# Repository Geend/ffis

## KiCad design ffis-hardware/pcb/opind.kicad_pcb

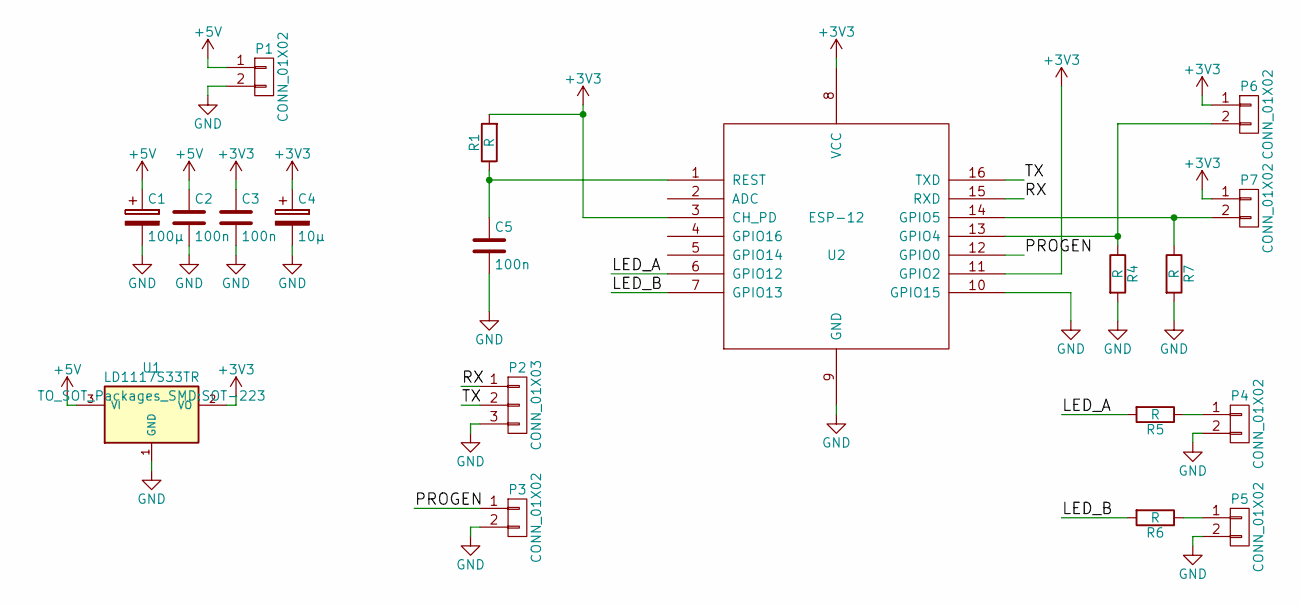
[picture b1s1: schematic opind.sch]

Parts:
C1: 100µ; c_elec_6.3x5.7
C2, C3, C5: 100n; C_0603_HandSoldering
C4: 10µ; c_elec_4x5.8
P1, P3, P4, P5, P6, P7: CONN_01X02; Pin_Header_Straight_1x02
P2: CONN_01X03; Pin_Header_Straight_1x03
R1, R4, R5, R6, R7: R; R_0603_HandSoldering
U1: LD1117S33TR; SOT-223
U2: ESP-12

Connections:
+3V3: C3.1, C4.1, P6.1, P7.1, R1.2, U1.2 (VO), U2.3 (CH_PD), U2.8 (VCC), U2.11 (GPIO2)
+5V: C1.1, C2.1, P1.1, U1.3 (VI)
/LED_A: R5.2, U2.6 (GPIO12)
/LED_B: R6.2, U2.7 (GPIO13)
/PROGEN: P3.1, U2.12 (GPIO0)
/RX: P2.1, U2.15 (RXD)
/TX: P2.2, U2.16 (TXD)
GND: C1.2, C2.2, C3.2, C4.2, C5.2, P1.2, P2.3, P3.2, P4.2, P5.2, R4.2, R7.2, U1.1 (GND), U2.9 (GND), U2.10 (GPIO15)
unnamed: C5.1, R1.1, U2.1 (REST)
unnamed: P4.1, R5.1
unnamed: P5.1, R6.1
unnamed: P6.2, R4.1, U2.13 (GPIO4)
unnamed: P7.2, R7.1, U2.14 (GPIO5)

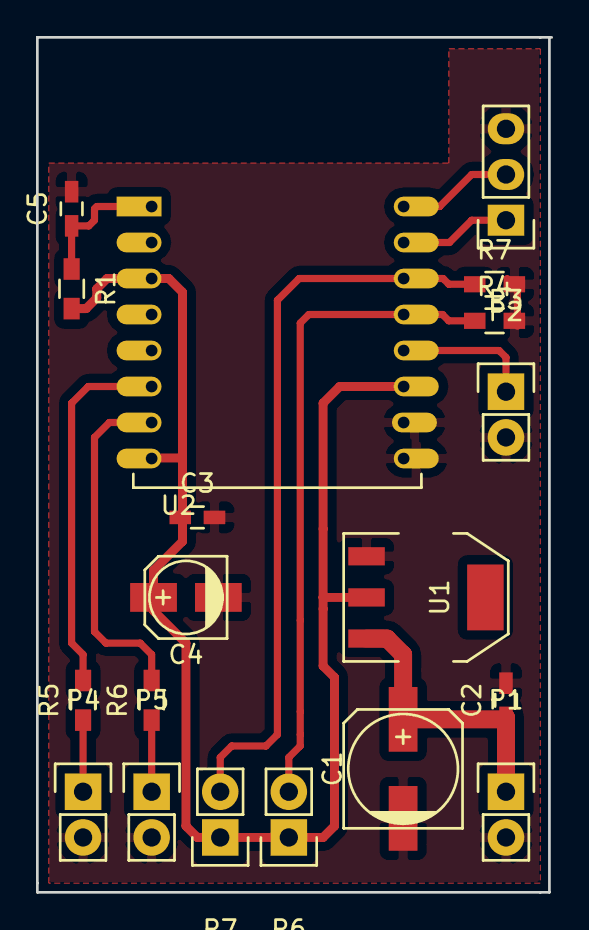
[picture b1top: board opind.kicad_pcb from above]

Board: 2 copper layers, 28.6 x 47.5 mm, 19 parts (0 on the bottom side), 13 nets.

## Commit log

2017-08-08 Initial commit after switch to gradle multi-project
2017-08-12 Changed to gradle composite-build
2017-08-12 Change application.properties key names
2017-08-12 Added central ffis specific json decoder class
2017-08-12 Switched from joda time to the ol'trusty java.util.Date, because timezones are insane
2017-08-12 Added joomla module
2017-08-16 Changed android target sdk to 26
2017-08-16 Added observer for local state
2017-08-16 Minor code cleanup
2017-08-17 Some more cleanup and added todos
2017-08-17 Added a ffis specific jackson ObjectMapper in common project
2017-08-19 Added silent notifications
2017-08-19 Preperation vor webservice 0.0.8 and app 1.5 release
2017-11-19 Added new gradlew
2018-01-26 Added hardware related parts
2018-01-26 Changed .gitignore
2018-03-13 Weahter changes
